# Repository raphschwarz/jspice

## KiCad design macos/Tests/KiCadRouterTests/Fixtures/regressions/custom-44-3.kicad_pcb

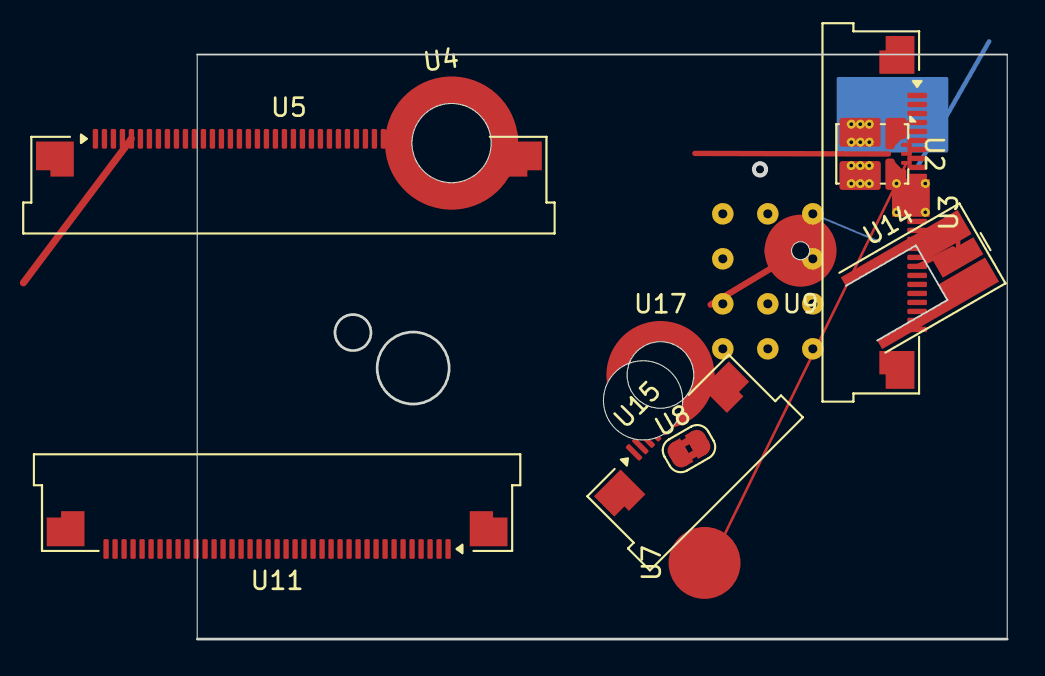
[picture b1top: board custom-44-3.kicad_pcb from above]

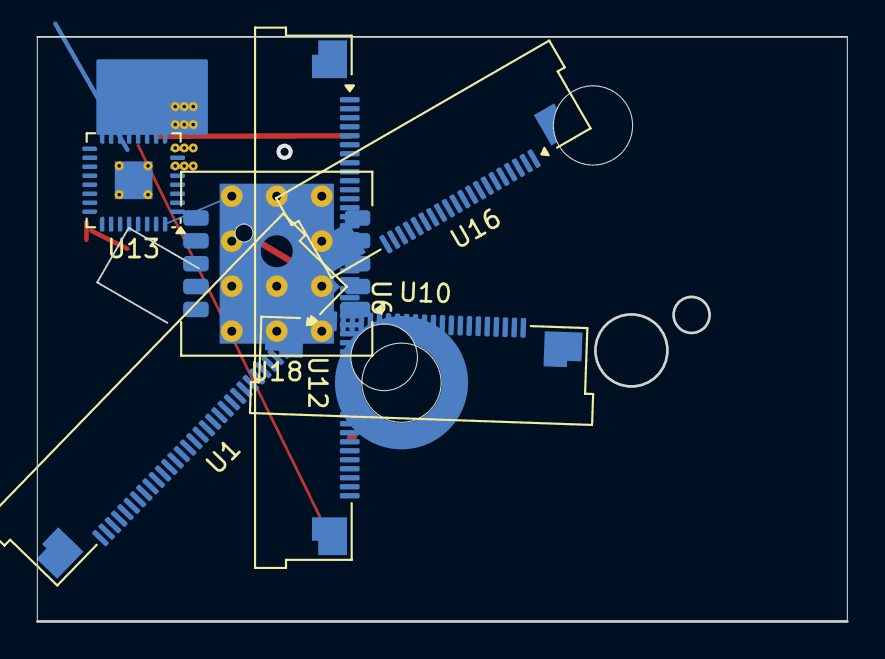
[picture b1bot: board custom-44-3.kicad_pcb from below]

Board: 2 copper layers, 45.0 x 32.5 mm, 18 parts (7 on the bottom side), 11 nets.

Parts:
U1: Amphenol_F32Q-1A7x1-11033_1x33-1MP_P0.5mm_Horizon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; Amphenol_F32Q-1A7x1-11033_1x33-1MP_P0.5mm_Horizontal
U2: Texas_RDX0007A_QFN-FCMOD-7-3.3x4mm-P0.5mm_4EP
U3: Amphenol_F32Q-1A7x1-11027_1x27-1MP_P0.5mm_Horizon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; Amphenol_F32Q-1A7x1-11027_1x27-1MP_P0.5mm_Horizontal
U4: Mounting_Wuerth_WA-SMSI-M3_H16mm_9774160360
U5: Amphenol_F32Q-1A7x1-11044_1x44-1MP_P0.5mm_Horizon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; Amphenol_F32Q-1A7x1-11044_1x44-1MP_P0.5mm_Horizontal
U6: Amphenol_F32Q-1A7x1-11045_1x45-1MP_P0.5mm_Horizon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; Amphenol_F32Q-1A7x1-11045_1x45-1MP_P0.5mm_Horizontal
U7: Mounting_Wuerth_WA-SMSI-M1.6_H4mm_ThreadDepth2mm_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; Mounting_Wuerth_WA-SMSI-M1.6_H4mm_ThreadDepth2mm_NoNPTH_977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
U8: SolderJumper-2_P1.3mm_Bridged2Bar_RoundedPad1.0x1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; SolderJumper-2_P1.3mm_Bridged2Bar_RoundedPad1.0x1.5mm
U9: Mounting_Wuerth_WA-SMSI-M1.6_H2.5mm_ThreadDepth1.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; Mounting_Wuerth_WA-SMSI-M1.6_H2.5mm_ThreadDepth1.5mm_977302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
U10: Amphenol_F32R-1A7x1-11023_1x23-1MP_P0.5mm_Horizon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; Amphenol_F32R-1A7x1-11023_1x23-1MP_P0.5mm_Horizontal
U11: Amphenol_F32Q-1A7x1-11039_1x39-1MP_P0.5mm_Horizon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; Amphenol_F32Q-1A7x1-11039_1x39-1MP_P0.5mm_Horizontal
U12: Mounting_Wuerth_WA-SMSR-M3_H2.6mm_ReverseMount_97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; Mounting_Wuerth_WA-SMSR-M3_H2.6mm_ReverseMount_9775026360
U13: TQFN-32-1EP_5x5mm_P0.5mm_EP2.1x2.1mm_ThermalVias
U14: MMCX_Molex_73415-0961_Horizontal_1.6mm-PCB
U15: Amphenol_F32Q-1A7x1-11009_1x09-1MP_P0.5mm_Horizon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; Amphenol_F32Q-1A7x1-11009_1x09-1MP_P0.5mm_Horizontal
U16: Amphenol_F32R-1A7x1-11020_1x20-1MP_P0.5mm_Horizon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; Amphenol_F32R-1A7x1-11020_1x20-1MP_P0.5mm_Horizontal
U17: Mounting_Wuerth_WA-SMSI-M2.5_H5.5mm_9774055151
U18: OriginGPS_ORG1510

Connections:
/net3: U1.6, U1.7, U1.22, U2.5, U4.1, U5.14, U5.33, U5.35, U6.1, U6.7, U6.13, U6.15, U6.27, U6.33, U10.MP, U11.8, U11.MP, U13.13, U13.23, U13.29, U15.3, U16.17, U18.1, U18.10
/sub/clk: U1.2, U1.5, U1.20, U1.33, U2.1, U3.5, U5.34, U6.5, U6.6, U6.10, U6.17, U6.21, U6.37, U6.39, U11.5, U11.23, U11.27, U13.2, U13.20, U13.33, U16.MP, U17.1, U18.3, U18.11
D7: U3.7, U3.8, U3.14, U5.19, U5.21, U5.40, U5.42, U6.4, U6.19, U6.22, U6.30, U11.13, U11.29, U13.24, U16.10, U18.7, U18.11
GND: U1.9, U1.16, U3.1, U3.2, U3.4, U3.11, U3.19, U3.24, U4.1, U5.4, U5.11, U5.18, U5.39, U5.41, U6.3, U6.24, U6.28, U6.45, U7.1, U9.1, U10.3, U10.15, U10.21, U10.23, U11.9, U11.17, U11.18, U11.21, U13.8, U13.28, U15.MP, U16.2, U16.6, U18.11
N1: U1.24, U3.15, U3.18, U3.MP, U5.17, U5.37, U6.12, U6.14, U6.29, U6.36, U6.41, U10.11, U10.22, U11.4, U11.6, U11.32, U11.36, U13.10, U13.31, U13.33, U16.9, U16.18, U18.11
N2: U1.1, U1.14, U1.28, U3.22, U3.MP, U5.6, U6.18, U6.43, U8.1, U8.2, U10.6, U10.17, U10.18, U10.MP, U11.24, U13.11, U15.6, U16.7, U16.19, U16.MP, U18.11
N3: U2.2, U3.12, U3.25, U4.1, U5.5, U5.8, U5.32, U6.35, U10.5, U10.9, U11.2, U11.20, U11.28, U11.37, U11.39, U12.1, U13.25, U16.12, U16.14, U18.5, U18.11
PWR1: U1.19, U2.6, U3.10, U5.1, U5.2, U5.15, U5.26, U5.28, U5.31, U6.25, U10.2, U11.30, U11.38, U11.MP, U12.1, U13.12, U13.14, U13.16, U13.19, U13.33, U14.2, U16.15, U17.1, U18.8, U18.11
SIG1: U1.17, U1.25, U1.30, U3.9, U3.27, U4.1, U5.16, U5.20, U5.36, U5.44, U6.20, U6.23, U6.26, U6.MP, U10.8, U10.14, U10.20, U11.15, U12.1, U13.9, U13.15, U13.17, U15.7, U16.1, U16.5, U16.8, U16.13, U17.1, U18.6
SIG2: U1.3, U1.15, U1.18, U1.23, U1.27, U2.7, U3.6, U3.20, U5.3, U5.30, U5.38, U5.43, U5.MP, U6.31, U10.1, U11.10, U11.14, U11.16, U11.19, U11.22, U13.1, U13.6, U13.21, U14.1, U14.2, U15.1, U15.9, U18.11
VCC: U1.12, U3.3, U6.9, U6.34, U6.42, U6.44, U10.7, U11.1, U13.4, U13.18, U13.27, U13.32, U15.8, U16.4, U16.20, U18.11

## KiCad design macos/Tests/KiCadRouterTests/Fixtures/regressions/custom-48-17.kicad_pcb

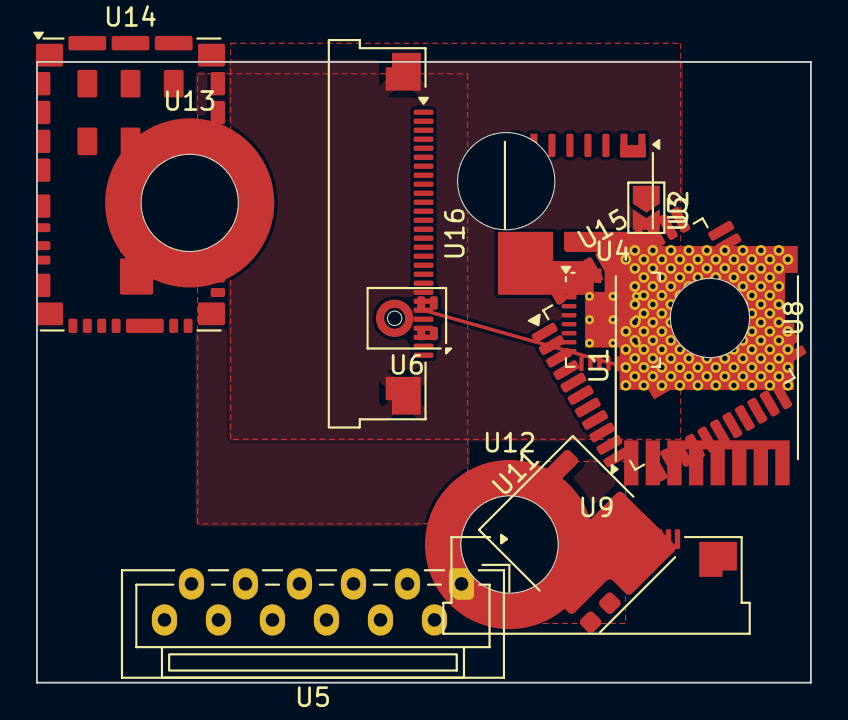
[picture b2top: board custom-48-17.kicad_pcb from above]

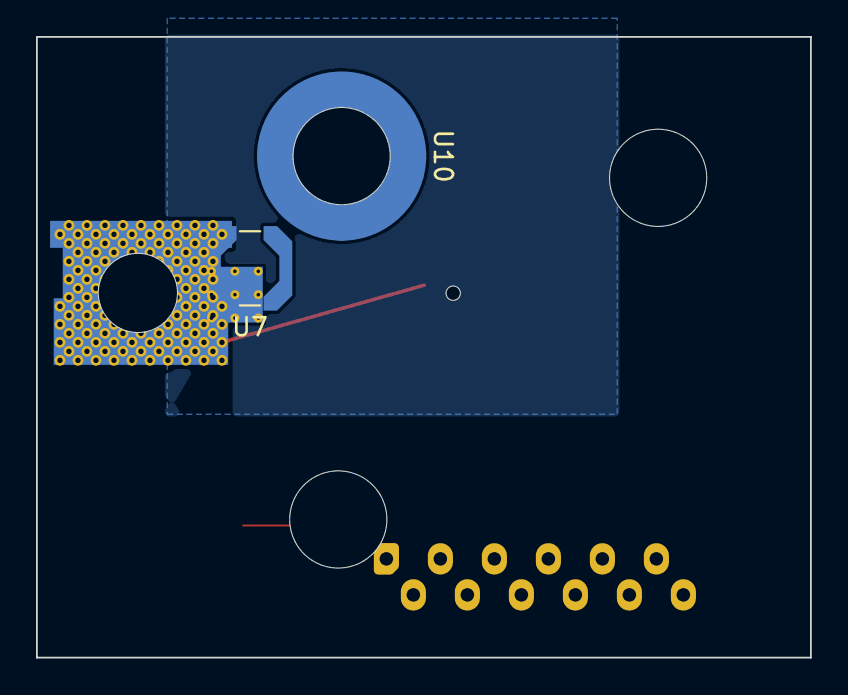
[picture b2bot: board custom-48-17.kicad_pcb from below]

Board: 2 copper layers, 43.0 x 34.5 mm, 16 parts (2 on the bottom side), 12 nets.

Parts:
U1: Infineon_PG-HSOF-8-2_ThermalVias2
U2: SolderJumper-2_P1.3mm_Open_TrianglePad1.0x1.5mm
U3: Infineon_PG-TISON-8-5
U4: TQFN-32-1EP_5x5mm_P0.5mm_EP3.1x3.1mm_ThermalVias
U5: JST_ZE_B12B-ZESK-D_1x12_P1.50mm_Vertical
U6: Infineon_PG-LLGA-5-2
U7: L_Coilcraft_LPS4414
U8: Mounting_Wuerth_WA-SMST-3.3mm_H13mm_9774130960
U9: Amphenol_F32Q-1A7x1-11019_1x19-1MP_P0.5mm_Horizon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; Amphenol_F32Q-1A7x1-11019_1x19-1MP_P0.5mm_Horizontal
U10: Mounting_Wuerth_WA-SMSI-M4_H10mm_9774100482
U11: GaN_Systems_GaNPX-4_7x8.4mm
U12: Mounting_Wuerth_WA-SMSI-M4_H3mm_9774030482
U13: Mounting_Wuerth_WA-SMSI-M4_H5mm_9774050482
U14: Texas_QFN-41_10x16mm
U15: TQFP-44-1EP_10x10mm_P0.8mm_EP4.5x4.5mm
U16: Amphenol_F32R-1A7x1-11028_1x28-1MP_P0.5mm_Horizon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; Amphenol_F32R-1A7x1-11028_1x28-1MP_P0.5mm_Horizontal

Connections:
/net3: U1.4, U4.1, U4.14, U4.23, U5.10, U7.2, U11.1, U14.13, U14.14, U14.18, U14.22, U14.34, U16.21, U16.26, U16.MP
/sub/clk: U1.4, U4.7, U4.27, U5.8, U6.2, U9.9, U9.10, U9.MP, U12.1, U14.11, U15.12, U15.36, U16.11, U16.15, U16.19
D7: U1.4, U2.1, U3.5, U4.2, U4.33, U14.36, U15.2, U15.9, U15.26, U16.14
D12: U1.4, U3.1, U5.11, U8.1, U9.7, U9.12, U9.MP, U13.1, U14.28, U14.30, U15.25, U15.28, U16.3
N1: U1.4, U4.20, U4.29, U4.32, U4.33, U8.1, U10.1, U11.2, U14.2, U14.9, U14.10, U15.3, U15.15, U15.20, U15.32, U16.6, U16.9
N2: U1.4, U4.10, U4.17, U4.18, U4.31, U4.33, U5.9, U9.19, U12.1, U13.1, U14.4, U14.5, U14.17, U14.27, U14.32, U15.17, U15.22, U15.43, U16.1, U16.23
N3: U1.4, U4.9, U5.3, U9.16, U14.23, U14.33, U15.37, U15.39, U15.41
PWR1: U1.2, U1.4, U4.3, U6.1, U9.13, U10.1, U12.1, U14.16, U14.24, U15.18, U15.33, U16.18, U16.24
PWR_5V: U1.4, U3.4, U4.33, U5.12, U7.1, U13.1, U14.12, U14.25, U14.26, U14.35, U14.39, U15.19, U15.35, U16.13, U16.16, U16.17, U16.20
SIG1: U1.1, U1.4, U4.22, U4.25, U9.2, U9.3, U9.17, U10.1, U14.8, U15.34, U15.40, U16.2, U16.12
SIG2: U1.4, U2.2, U3.2, U4.8, U5.7, U9.15, U14.6, U14.7, U15.1, U15.4, U15.27, U16.5
VCC: U1.4, U4.6, U4.11, U4.19, U4.33, U5.1, U8.1, U9.4, U9.8, U11.2, U14.1, U14.15, U14.19, U14.29, U14.41, U15.5, U15.6, U15.14, U15.16, U15.21, U15.29, U15.30, U16.22

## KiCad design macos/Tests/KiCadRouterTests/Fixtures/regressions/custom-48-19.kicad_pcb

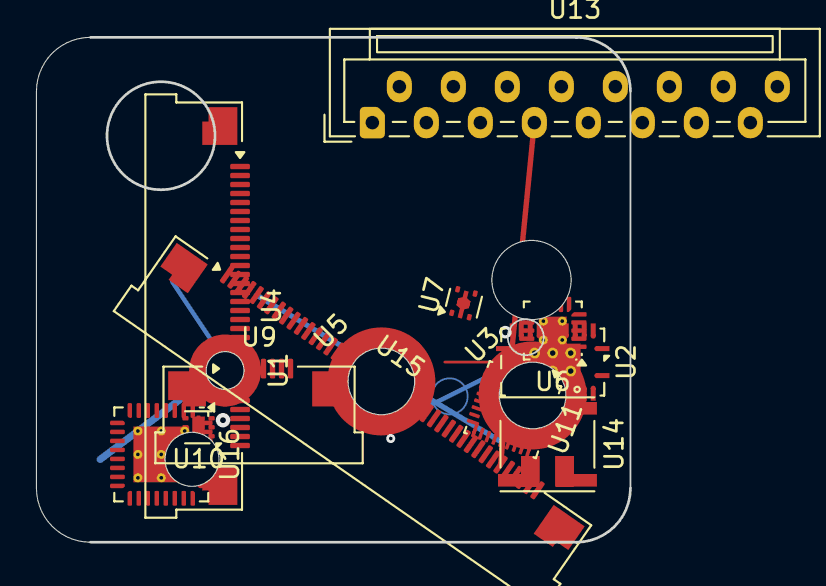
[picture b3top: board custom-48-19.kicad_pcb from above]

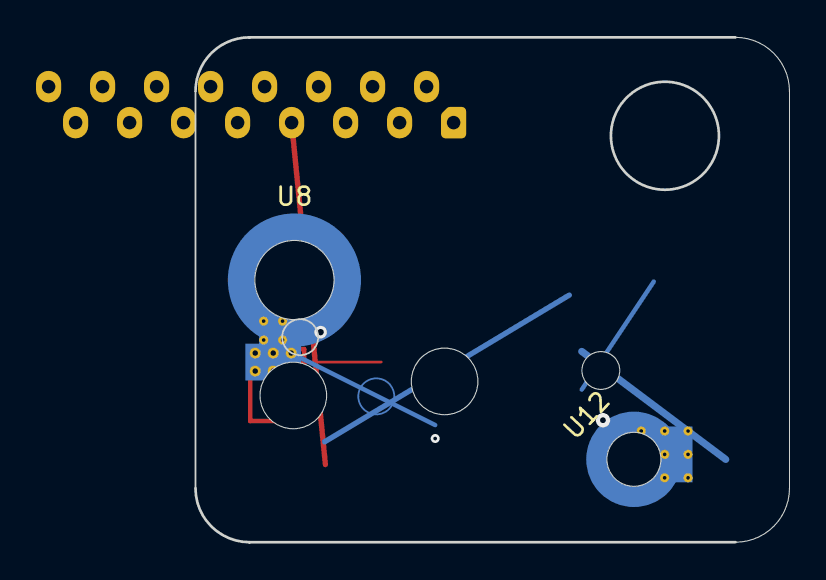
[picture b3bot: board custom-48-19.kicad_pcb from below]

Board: 2 copper layers, 33.0 x 28.0 mm, 16 parts (2 on the bottom side), 4 nets.

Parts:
U1: Mounting_Wuerth_WA-SMSI-M1.6_H3mm_9774030633
U2: Texas_RGY_R-PVQFN-N24_EP2.05x3.1mm_ThermalVias
U3: Mounting_Wuerth_WA-SMST-2.7mm_H4mm_9774040951
U4: Amphenol_F32R-1A7x1-11032_1x32-1MP_P0.5mm_Horizon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; Amphenol_F32R-1A7x1-11032_1x32-1MP_P0.5mm_Horizontal
U5: Mounting_Wuerth_WA-SMST-2.7mm_H3mm_9774030951
U6: VQFN-20-1EP_3x3mm_P0.45mm_EP1.55x1.55mm_ThermalVi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; VQFN-20-1EP_3x3mm_P0.45mm_EP1.55x1.55mm_ThermalVias
U7: HVSOF5
U8: Mounting_Wuerth_WA-SMST-3.3mm_H15mm_9774150960
U9: Amphenol_F32R-1A7x1-11008_1x08-1MP_P0.5mm_Horizon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; Amphenol_F32R-1A7x1-11008_1x08-1MP_P0.5mm_Horizontal
U10: Skyworks_SKY65404-31
U11: Texas_RQM0029A_VQFN-29_4x4mm_P0.4mm
U12: Mounting_Wuerth_WA-SMSI-M2_H2mm_9774020243
U13: JST_ZE_B16B-ZESK-D_1x16_P1.50mm_Vertical
U14: L_CommonModeChoke_Murata_DLW5BTMxxxSQ2x_5x5mm
U15: Amphenol_F32R-1A7x1-11043_1x43-1MP_P0.5mm_Horizon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; Amphenol_F32R-1A7x1-11043_1x43-1MP_P0.5mm_Horizontal
U16: TQFN-32-1EP_5x5mm_P0.5mm_EP3.1x3.1mm_ThermalVias

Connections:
D12: U1.1, U2.1, U2.2, U2.14, U2.18, U2.19, U2.23, U4.4, U4.22, U4.MP, U5.1, U6.4, U6.7, U6.8, U6.9, U6.16, U6.18, U6.21, U7.5, U8.1, U9.MP, U10.3, U10.5, U10.7, U11.3, U11.12, U11.15, U11.16, U11.19, U11.25, U11.26, U11.29, U12.1, U13.7, U13.9, U13.10, U13.15, U14.3, U15.3, U15.8, U15.10, U15.12, U15.13, U15.15, U15.23, U15.27, U15.37, U15.40, U15.43, U16.5, U16.6, U16.16, U16.17, U16.18, U16.22, U16.24, U16.27, U16.33
GND: U1.1, U2.4, U2.7, U2.10, U2.17, U3.1, U4.2, U4.17, U4.19, U4.21, U4.23, U4.30, U4.32, U4.MP, U6.2, U6.5, U6.19, U6.21, U7.4, U8.1, U9.5, U9.7, U11.4, U11.5, U13.4, U13.11, U13.14, U14.1, U15.4, U15.6, U15.9, U15.11, U15.16, U15.21, U15.29, U15.31, U15.32, U15.34, U15.38, U15.MP, U16.2, U16.3, U16.10, U16.19, U16.20, U16.29, U16.31
N2: U2.6, U2.11, U2.13, U2.24, U2.25, U3.1, U4.3, U4.5, U4.6, U4.7, U4.8, U4.10, U4.11, U4.12, U4.15, U4.24, U4.31, U5.1, U6.3, U6.10, U6.12, U6.21, U9.1, U9.6, U9.MP, U10.2, U11.6, U11.7, U11.10, U11.22, U11.23, U11.28, U13.2, U15.1, U15.14, U15.20, U15.25, U15.26, U15.41, U16.1, U16.4, U16.8, U16.14, U16.23, U16.30, U16.33
VCC: U1.1, U2.3, U2.12, U2.22, U2.25, U4.1, U4.13, U4.14, U4.18, U4.25, U4.26, U4.27, U5.1, U6.6, U6.13, U6.20, U6.21, U7.1, U9.2, U9.8, U10.4, U11.2, U11.9, U11.11, U11.13, U11.17, U11.21, U11.24, U12.1, U13.3, U13.5, U13.8, U13.12, U13.13, U15.17, U15.28, U15.30, U15.36, U15.39, U15.42, U16.11, U16.12, U16.13, U16.15, U16.25, U16.26, U16.28, U16.33

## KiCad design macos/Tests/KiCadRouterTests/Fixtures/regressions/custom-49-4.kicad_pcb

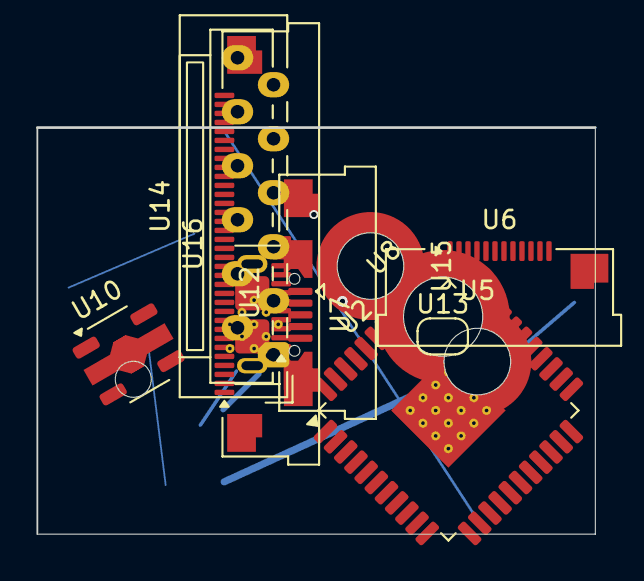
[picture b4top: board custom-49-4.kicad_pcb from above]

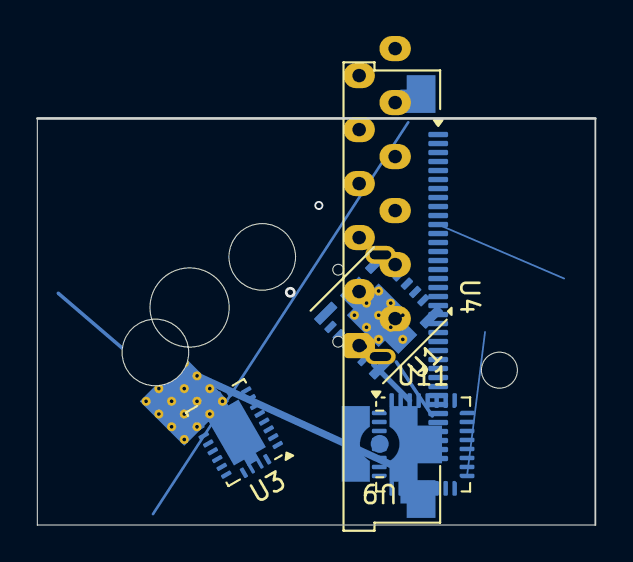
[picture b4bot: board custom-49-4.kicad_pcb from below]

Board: 2 copper layers, 31.0 x 22.6 mm, 16 parts (5 on the bottom side), 12 nets.

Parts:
U1: Texas_B3QFN-14-1EP_5x5.5mm_P0.65mm_ThermalVia
U2: TQFP-44-1EP_10x10mm_P0.8mm_EP4.5x4.5mm_ThermalVias
U3: Texas_VQFN-RHL-20
U4: Amphenol_F32R-1A7x1-11037_1x37-1MP_P0.5mm_Horizon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; Amphenol_F32R-1A7x1-11037_1x37-1MP_P0.5mm_Horizontal
U5: Mounting_Wuerth_WA-SMSI-M2.5_H3.5mm_9774035151
U6: Amphenol_F32R-1A7x1-11012_1x12-1MP_P0.5mm_Horizon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; Amphenol_F32R-1A7x1-11012_1x12-1MP_P0.5mm_Horizontal
U7: USB_Micro-B_XKB_U254-051T-4BH83-F1S
U8: Mounting_Wuerth_WA-SMSI-M3_H6mm_9774060360
U9: WR-MMCX_Wuerth_66011102111302_Horizontal
U10: SOT-89-5
U11: Texas_RHB0032M_VQFN-32-1EP_5x5mm_P0.5mm_EP2.1x2.1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; Texas_RHB0032M_VQFN-32-1EP_5x5mm_P0.5mm_EP2.1x2.1mm
U12: Amphenol_F32Q-1A7x1-11013_1x13-1MP_P0.5mm_Horizon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; Amphenol_F32Q-1A7x1-11013_1x13-1MP_P0.5mm_Horizontal
U13: SolderJumper-2_P1.3mm_Bridged_RoundedPad1.0x1.5mm
U14: JST_ZE_B12B-ZESK-D_1x12_P1.50mm_Vertical
U15: Mounting_Wuerth_WA-SMST-2.7mm_H6.5mm_9774065951
U16: Amphenol_F32Q-1A7x1-11034_1x34-1MP_P0.5mm_Horizon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; Amphenol_F32Q-1A7x1-11034_1x34-1MP_P0.5mm_Horizontal

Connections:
/net3: U1.7, U2.4, U2.16, U2.23, U2.29, U3.2, U3.4, U3.14, U4.5, U4.17, U4.28, U7.SH, U11.8, U12.11, U14.2, U14.11, U15.1, U16.9, U16.25
/sub/clk: U1.2, U1.6, U1.12, U2.1, U2.33, U2.41, U2.45, U3.21, U8.1, U9.1, U10.1, U11.4, U11.19, U11.27, U11.33, U12.3, U16.22, U16.31
D7: U1.15, U2.11, U2.27, U2.30, U2.38, U2.45, U3.1, U3.8, U3.12, U6.5, U7.4, U10.2, U11.1, U11.12, U11.14, U16.11, U16.28
D12: U1.14, U1.15, U2.5, U2.7, U2.21, U2.24, U2.45, U3.16, U4.12, U4.15, U4.25, U4.27, U6.12, U11.31, U11.32, U12.1, U12.9, U12.MP, U16.7, U16.27, U16.33
N1: U1.5, U2.17, U2.42, U2.45, U3.21, U4.4, U4.14, U4.18, U4.26, U8.1, U11.7, U11.16, U11.24, U12.8, U14.10
N2: U1.13, U2.19, U3.21, U4.22, U4.24, U4.34, U7.SH, U8.1, U11.30, U12.4, U12.7, U13.2, U14.4, U16.14, U16.20
N3: U1.11, U1.15, U3.17, U4.7, U4.35, U4.MP, U6.2, U7.2, U14.1, U16.15, U16.19, U16.21, U16.32
PWR1: U2.9, U2.45, U4.9, U4.10, U4.20, U8.1, U11.2, U11.15, U11.23, U11.29, U16.6, U16.17, U16.29, U16.MP
PWR_5V: U1.8, U1.15, U2.3, U2.20, U2.45, U4.1, U4.37, U6.1, U6.10, U7.3, U7.SH, U11.6, U11.13, U12.6, U14.9, U14.12, U16.2, U16.23, U16.24
SIG1: U1.15, U2.25, U2.26, U2.45, U3.6, U3.18, U3.20, U4.29, U4.30, U4.36, U5.1, U6.3, U6.9, U6.MP, U7.SH, U11.5, U14.3, U16.5
SIG2: U1.9, U1.10, U2.6, U2.37, U2.45, U3.5, U3.7, U3.15, U4.2, U4.6, U4.8, U4.16, U4.31, U5.1, U6.7, U11.3, U11.18, U11.22, U12.10, U13.1, U16.1, U16.18, U16.30
VCC: U1.3, U1.4, U1.15, U2.10, U2.12, U2.14, U2.15, U2.18, U2.22, U2.32, U2.45, U3.10, U3.21, U4.11, U4.13, U4.19, U4.23, U7.SH, U10.4, U10.5, U11.9, U11.25, U16.8

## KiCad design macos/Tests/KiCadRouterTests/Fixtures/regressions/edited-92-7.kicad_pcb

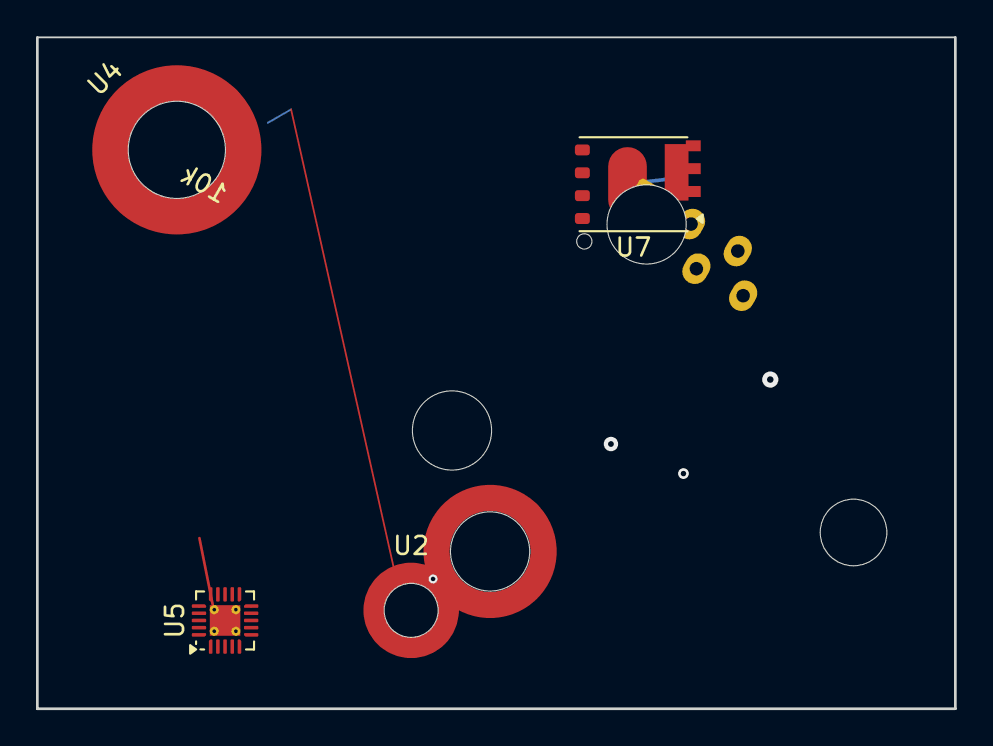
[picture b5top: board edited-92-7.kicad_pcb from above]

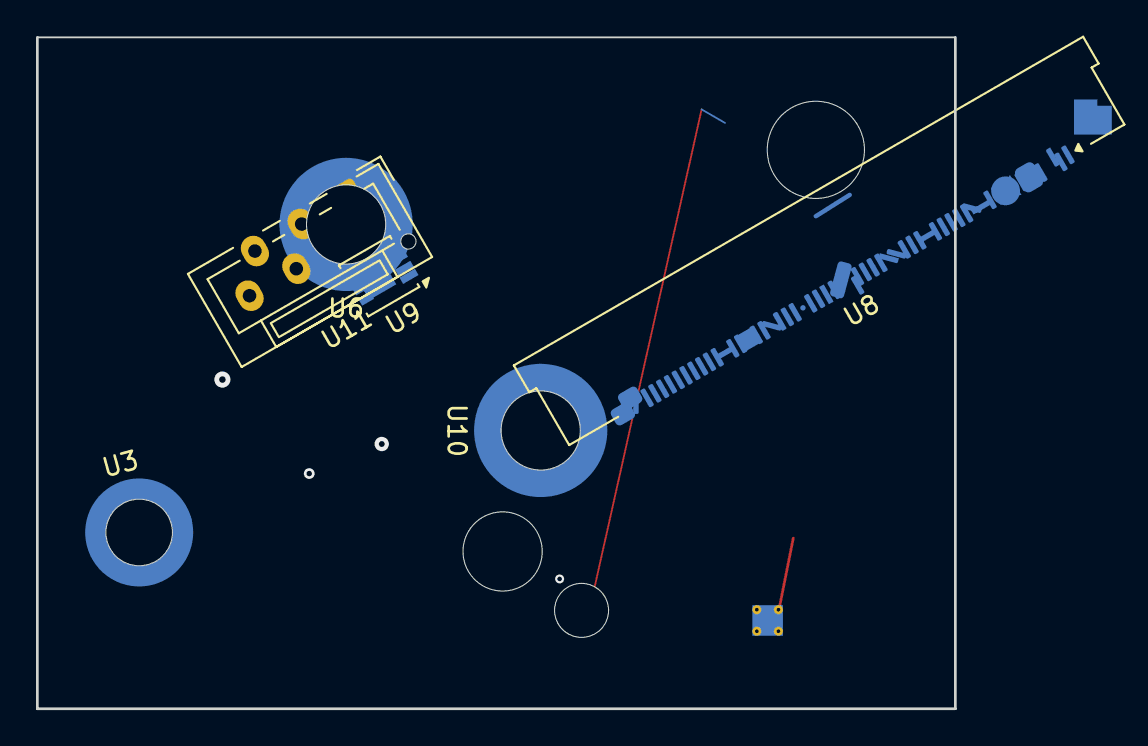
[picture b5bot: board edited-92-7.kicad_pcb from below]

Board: 2 copper layers, 51.0 x 37.3 mm, 11 parts (6 on the bottom side), 5 nets.

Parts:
U1: 4.7µF; Mounting_Wuerth_WA-SMSR-3.2mm_H7.6mm_ReverseMount_9775076960
U2: Mounting_Wuerth_WA-SMST-2.25mm_H2.5mm_9774025943
U3: Mounting_Wuerth_WA-SMST-2.7mm_H4mm_9774040951
U4: Mounting_Wuerth_WA-SMST-4.5mm_H3mm_9774030982
U5: VQFN-20-1EP_3x3mm_P0.4mm_EP1.7x1.7mm_ThermalVias
U6: 4.7µF; Mounting_Wuerth_WA-SMST-3.3mm_H3mm_9774030960
U7: Infineon_PG-TISON-8-3
U8: 10k; Amphenol_F32Q-1A7x1-11058_1x58-1MP_P0.5mm_Horizontal
U9: 4.7µF; Vishay_PowerPAK_1212-8_Single
U10: JSpice "edited"; Mounting_Wuerth_WA-SMSI-M3_H8mm_9774080360
U11: JST_ZE_B06B-ZESK-1D_1x06_P1.50mm_Vertical

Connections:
/sub/clk: U2.1, U3.1, U5.18, U5.21, U8.5, U8.19, U8.21, U8.34, U8.46, U8.47, U8.57, U9.1, U10.1, U11.6
N2: U1.1, U5.4, U5.5, U5.17, U6.1, U7.2, U8.1, U8.17, U8.22, U8.27, U8.45, U8.MP, U9.4, U9.5
PWR1: U1.1, U3.1, U5.6, U5.10, U5.11, U5.13, U5.14, U5.20, U5.21, U6.1, U7.5, U8.1, U8.4, U8.8, U8.9, U8.12, U8.15, U8.35, U8.48, U8.50
PWR_5V: U1.1, U2.1, U4.1, U5.2, U5.21, U7.4, U7.6, U8.1, U8.7, U8.20, U8.24, U8.28, U8.36, U8.42, U8.MP, U9.2, U9.3, U10.1
SIG1: U2.1, U5.3, U5.7, U5.15, U5.16, U7.1, U8.1, U8.2, U8.6, U8.18, U8.29, U8.32, U8.33, U8.40, U8.43, U8.49, U8.54, U10.1, U11.3

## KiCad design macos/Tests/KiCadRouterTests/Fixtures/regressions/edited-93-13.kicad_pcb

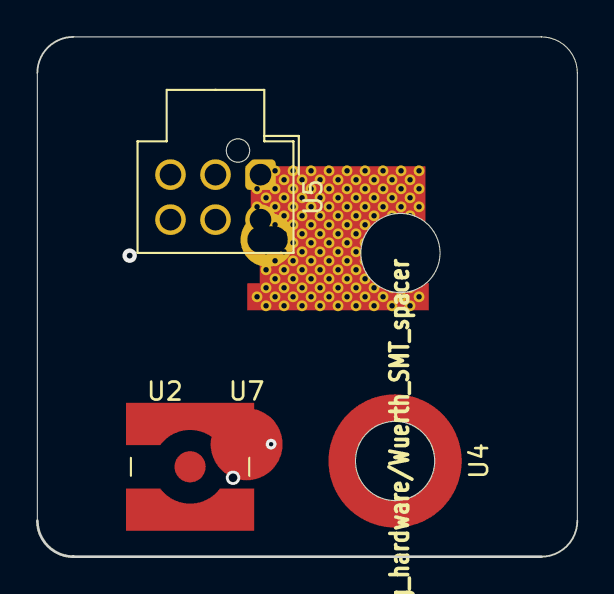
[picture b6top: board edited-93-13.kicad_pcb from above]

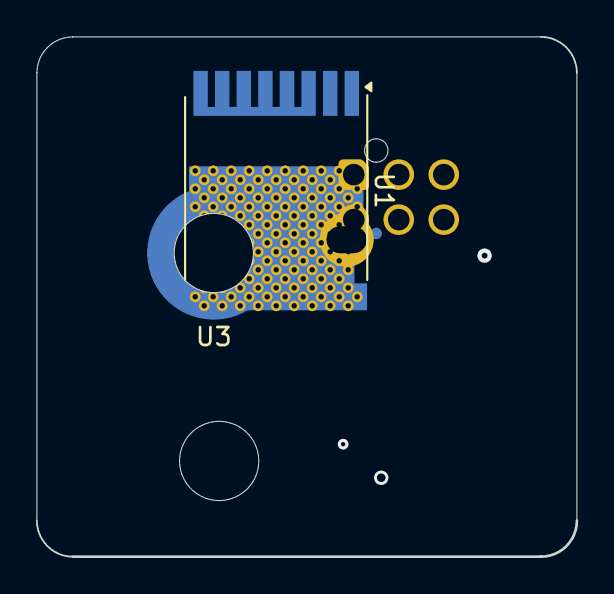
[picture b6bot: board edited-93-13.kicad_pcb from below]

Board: 2 copper layers, 30.0 x 28.9 mm, 7 parts (3 on the bottom side), 4 nets, no tracks yet.

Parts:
U1: Infineon_PG-HSOF-8-2_ThermalVias2
U2: SMA_Wurth_60312102114405_Vertical
U3: Mounting_Wuerth_WA-SMST-3.3mm_H8mm_9774080960
U4: Mounting_Wuerth_WA-SMSI-M3_H5mm_9774050360
U5: Molex_Nano-Fit_105310-xx06_2x03_P2.50mm_Vertical
U6: Mounting_Wuerth_WA-SMST-2.25mm_H5mm_9774050943
U7: Mounting_Wuerth_WA-SMSI-M1.6_H6mm_ThreadDepth2mm_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; Mounting_Wuerth_WA-SMSI-M1.6_H6mm_ThreadDepth2mm_NoNPTH_977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

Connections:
D7: U1.3, U1.4, U2.2, U3.1
N1: U1.1, U1.4, U3.1, U4.1, U5.1, U6.1
SIG1: U1.4, U3.1, U4.1, U5.5, U6.1, U7.1
VCC: U1.4, U5.2, U5.3

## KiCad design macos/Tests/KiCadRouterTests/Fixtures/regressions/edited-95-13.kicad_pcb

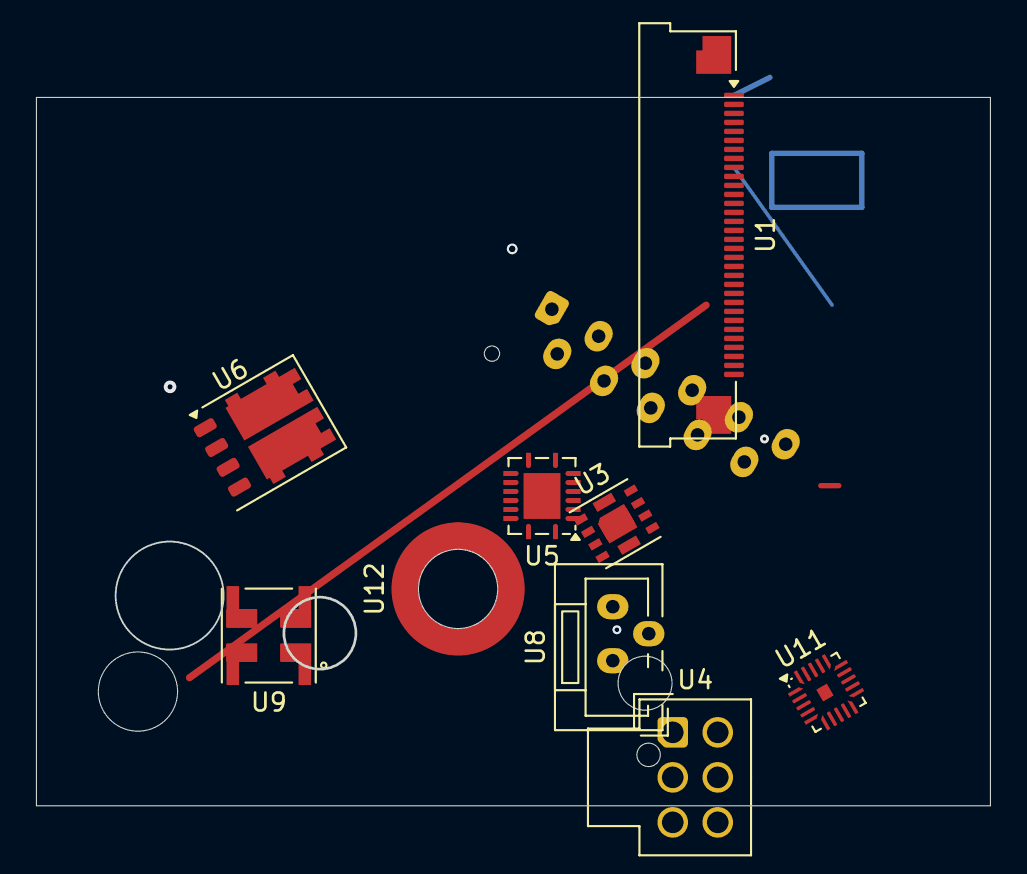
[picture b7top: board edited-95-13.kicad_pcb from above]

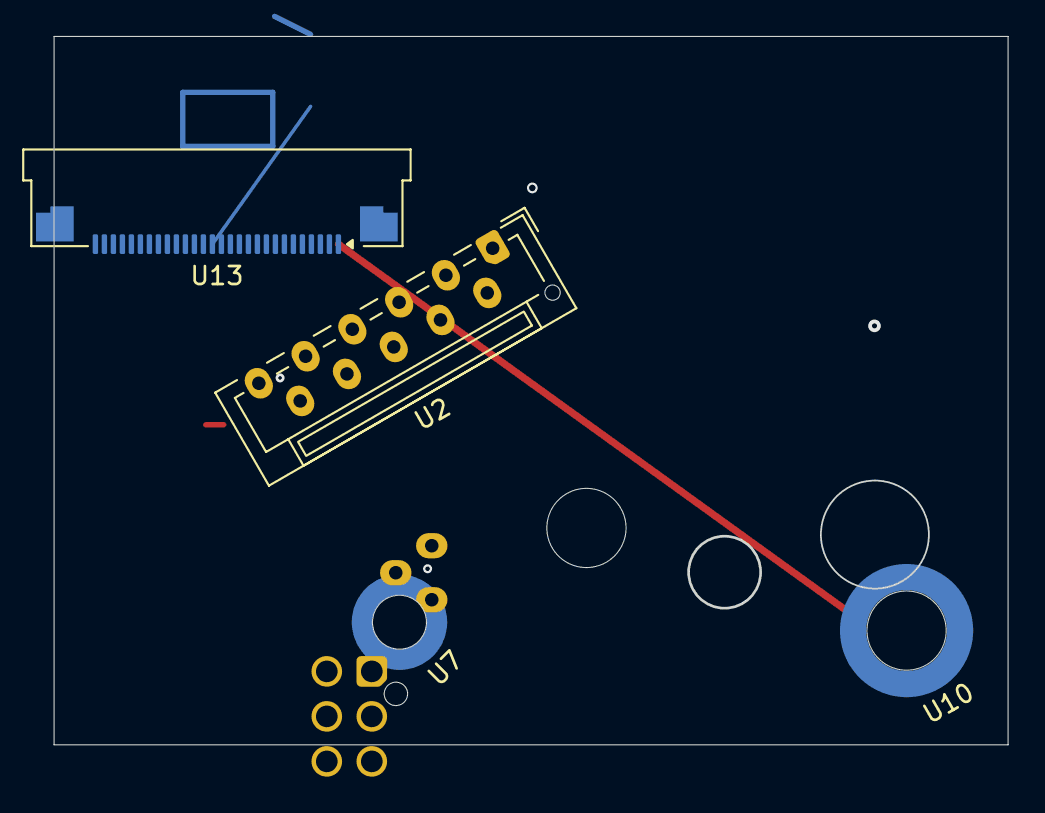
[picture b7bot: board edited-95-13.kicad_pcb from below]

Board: 2 copper layers, 53.0 x 39.4 mm, 13 parts (4 on the bottom side), 10 nets.

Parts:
U1: Amphenol_F32Q-1A7x1-11032_1x32-1MP_P0.5mm_Horizon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; Amphenol_F32Q-1A7x1-11032_1x32-1MP_P0.5mm_Horizontal
U2: JST_ZE_B11B-ZESK-1D_1x11_P1.50mm_Vertical
U3: Converter_DCDC_Cyntec_MUN12AD03-SH
U4: Molex_Nano-Fit_105310-xx06_2x03_P2.50mm_Vertical
U5: Texas_RGY_R-PVQFN-N16_EP2.05x2.55mm
U6: ST_PowerFLAT-6L_5x6mm_P1.27mm
U7: Mounting_Wuerth_WA-SMST-2.25mm_H6mm_9774060943
U8: JST_ZE_B04B-ZESK-D_1x04_P1.50mm_Vertical
U9: L_CommonModeChoke_Murata_DLW5BTMxxxSQ2x_5x5mm
U10: Mounting_Wuerth_WA-SMSR-M3_H3.6mm_ReverseMount_97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; Mounting_Wuerth_WA-SMSR-M3_H3.6mm_ReverseMount_9775036360
U11: Texas_RJE0020A_VQFN-20-1EP_3x3mm_P0.45mm_EP0.675x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; Texas_RJE0020A_VQFN-20-1EP_3x3mm_P0.45mm_EP0.675x0.76mm
U12: Mounting_Wuerth_WA-SMSI-M3_H8mm_9774080360
U13: Amphenol_F32Q-1A7x1-11028_1x28-1MP_P0.5mm_Horizon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; Amphenol_F32Q-1A7x1-11028_1x28-1MP_P0.5mm_Horizontal

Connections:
/net3: U1.17, U1.18, U2.3, U3.9, U4.6, U5.10, U10.1, U11.3, U11.15, U11.16, U12.1, U13.11, U13.16, U13.28
D7: U1.3, U2.5, U2.11, U7.1, U8.4, U11.1, U11.4, U13.3, U13.14, U13.17, U13.21
D12: U1.2, U1.10, U1.14, U1.16, U1.MP, U3.11, U5.4, U6.1, U10.1, U11.6, U11.18, U13.1, U13.22, U13.23
GND: U1.23, U4.1, U5.8, U6.5, U10.1, U12.1, U13.4, U13.27
N1: U1.7, U1.13, U1.28, U1.30, U3.2, U3.4, U4.2, U5.5, U5.7, U7.1, U11.2, U11.17, U12.1
N2: U1.1, U1.26, U1.27, U1.29, U1.31, U3.5, U5.9, U5.11, U7.1, U9.3, U11.10, U13.13
N3: U2.8, U3.3, U3.6, U4.3, U9.1, U9.2, U11.9, U13.5, U13.7, U13.10, U13.18, U13.20, U13.MP
PWR1: U1.8, U5.12, U8.1, U8.2, U11.12, U11.14, U13.MP
PWR_5V: U1.5, U1.11, U2.7, U2.10, U3.1, U5.6, U5.14, U5.17, U9.4, U11.7, U11.11, U11.21, U13.12, U13.15
VCC: U1.6, U1.21, U1.25, U5.15, U5.16, U7.1, U11.5, U11.13, U11.19, U13.6, U13.8, U13.9, U13.25

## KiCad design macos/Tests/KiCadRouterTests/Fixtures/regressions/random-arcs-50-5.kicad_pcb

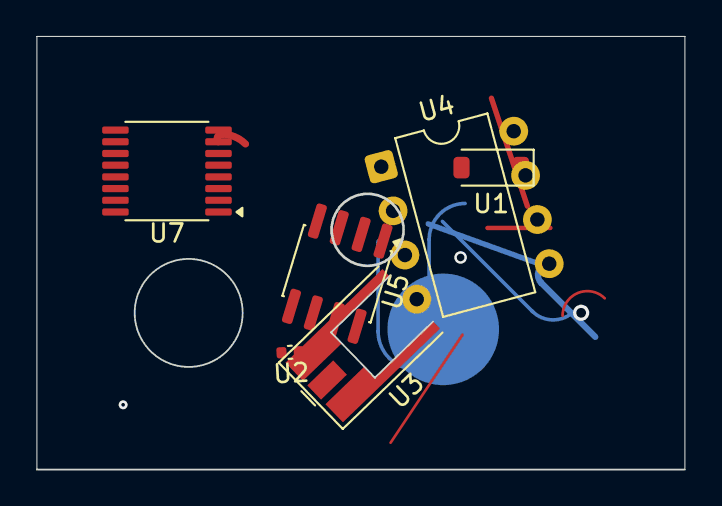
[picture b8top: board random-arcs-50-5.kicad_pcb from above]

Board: 2 copper layers, 36.0 x 24.1 mm, 7 parts (1 on the bottom side), 12 nets.

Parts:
U1: D_SOD-123
U2: C_0402_1005Metric
U3: MMCX_Molex_73415-0961_Horizontal_0.8mm-PCB
U4: DIP-8_W7.62mm
U5: SOIC-8_3.9x4.9mm_P1.27mm
U6: BGA-64_9.0x9.0mm_Layout10x10_P0.8mm
U7: TSSOP-16_4.4x5mm_P0.65mm

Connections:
/sub/clk: U3.2, U6.B1, U6.B6, U6.D9, U7.13
D7: U6.A2, U6.A6, U6.K1, U6.K7
D12: U6.A5, U6.F1, U6.H9, U6.K6, U7.1, U7.4
GND: U1.2, U5.1, U6.A7, U6.A9, U6.B3, U6.E9, U7.11
N1: U6.A1, U6.E2, U6.G1, U6.G2, U6.G9, U6.K4, U7.9
N2: U4.2, U4.6, U6.B8, U6.C9, U6.J1, U6.J3
N3: U4.5, U6.A8, U6.B9, U6.D2
PWR1: U4.8, U6.B2, U6.D10, U6.J6, U7.7
PWR_5V: U1.1, U2.2, U6.E1, U6.F10, U6.J7, U7.16
SIG1: U3.1, U4.1, U4.3, U4.7, U5.5, U6.A4, U6.B4, U6.G10, U6.H1, U7.3, U7.14
SIG2: U5.4, U5.7, U5.8, U6.B7, U6.F9, U6.H2, U6.J2, U6.J4, U6.J5, U7.10
VCC: U5.2, U6.A10, U6.B5, U6.K2, U6.K5, U7.2, U7.15
